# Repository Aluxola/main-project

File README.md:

# main-project
# Micro-mouse System Power and Sensor Subsystems
# Overview
This repository contains the design and implementation files for the Power and Sensor subsystems of a robotic system developed as part of the EEE3088F_2024 project. The Power subsystem manages power distribution, voltage regulation, and battery management, while the Sensor subsystem handles sensing and feedback for the robot's environment.

# Power Subsystem Features
Power distribution to motors and electronic components
Voltage regulation for stable operation
Battery management functions for efficient use
Current limiting and safety features
Power switching capabilities for control
Efficiency optimization for energy savings
# Sensor Subsystem Features
Wall sensing using infrared sensors
LED indicators for wall detection
Interface with the processor board for feedback
Low power consumption design
Reliability and accuracy in sensing wall proximity
# Contents
## Power Module:
### Schematics: 
Contains the schematic diagrams of the power module circuitry.
### PCB Design: 
Includes the PCB layout design files for manufacturing the power module.

## Sensor Module:
### Schematics: 
Contains the schematic diagrams of the sensor module circuitry.
### PCB Design: 
Includes the PCB layout design files for manufacturing the sensor module.
### Code: 
Firmware or software code for interfacing the sensor module with the processor board.
## Requirements
### Hardware: 
List of components required for building the power and sensor modules.
### Software: 
Tools and software required for programming, testing, and interfacing with the modules.

# Contributors
Alulutho Mthitshana

Tlangelani Tembe

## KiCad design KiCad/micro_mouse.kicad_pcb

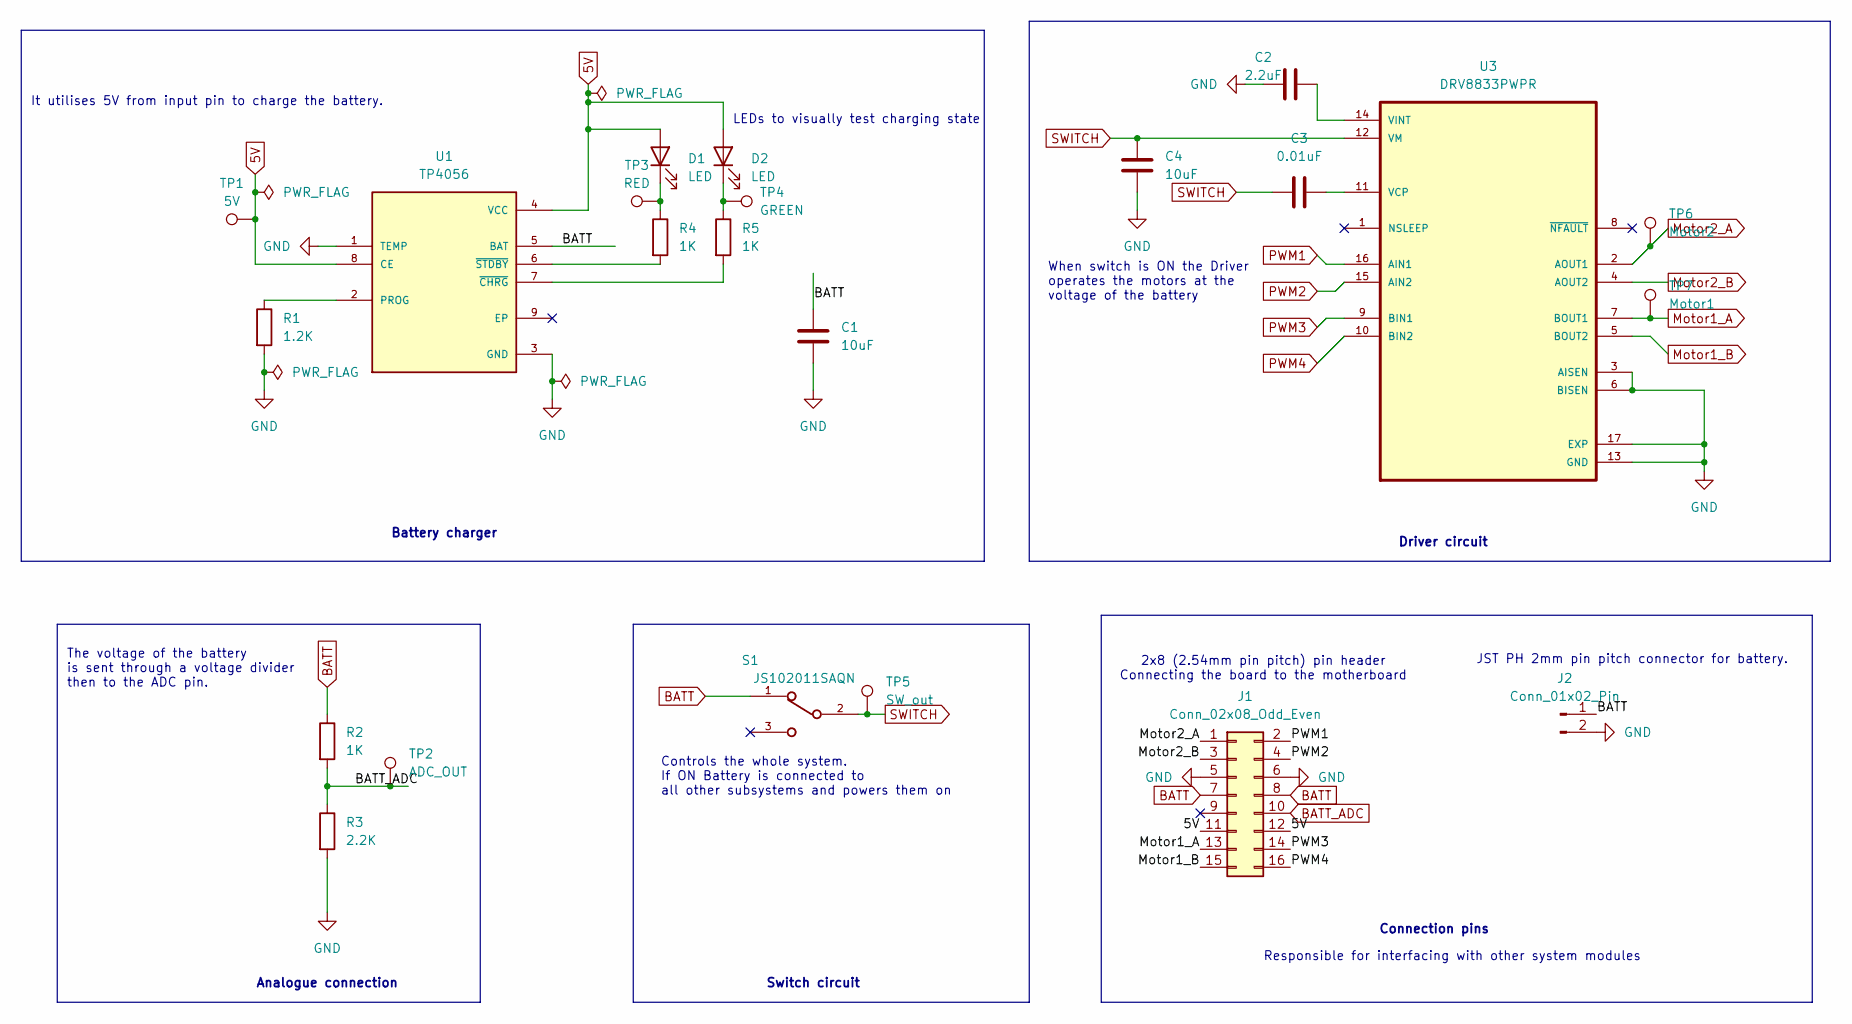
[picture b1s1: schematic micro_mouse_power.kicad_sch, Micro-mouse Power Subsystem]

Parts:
C1, C4: 10uF; C_0603_1608Metric
C2: 2.2uF; C_0603_1608Metric
C3: 0.01uF; C_0603_1608Metric
D1: LED; LED_0805_2012Metric
D2: LED; LED_0603_1608Metric
J1: Conn_02x08_Odd_Even; PinHeader_2x08_P2.54mm_Vertical
J2: Conn_01x02_Pin; JST_PH_B2B-PH-K_1x02_P2.00mm_Vertical
R1: 1.2K; R_0603_1608Metric
R2, R4, R5: 1K; R_0603_1608Metric
R3: 2.2K; R_0603_1608Metric
S1: JS102011SAQN; SW_JS102011SAQN
TP1: 5V; TestPoint_Pad_D1.5mm
TP2: ADC_OUT; TestPoint_Pad_D1.5mm
TP3: RED; TestPoint_Pad_D1.5mm
TP4: GREEN; TestPoint_Pad_D1.5mm
TP5: SW_out
TP6: Motor2; TestPoint_Pad_D1.5mm
TP7: Motor1; TestPoint_Pad_D1.5mm
U1: TP4056; SOP127P600X175-9N
U3: DRV8833PWPR; SOP65P640X120-16N; PARTREV E

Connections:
5V: D1.2 (A), D2.2 (A), J1.11, J1.12, TP1.1, U1.4 (VCC), U1.8 (CE)
BATT: C1.2, J1.7, J1.8, J2.1, R2.1, S1.1, U1.5 (BAT)
BATT_ADC: J1.10, R2.2, R3.1, TP2.1
GND: C1.1, C2.1, C4.2, J1.5, J1.6, J2.2, R1.2, R3.2, U1.1 (TEMP), U1.3 (GND), U3.3 (AISEN), U3.6 (BISEN), U3.13 (GND), U3.17 (EXP); also elsewhere on the board
Motor1_A: J1.13, TP7.1, U3.7 (BOUT1); also elsewhere on the board
Motor1_B: J1.15; also elsewhere on the board
Motor2_A: J1.1, TP6.1, U3.2 (AOUT1); also elsewhere on the board
Motor2_B: J1.3; also elsewhere on the board
unnamed: D1.1 (K), R4.1, TP3.1
unnamed: D2.1 (K), R5.1, TP4.1
unnamed: R1.1, U1.2 (PROG)
unnamed: R5.2, U1.7 (~CHRG)
unnamed: R4.2, U1.6 (~STDBY)
unnamed: C3.2, U3.11 (VCP)
unnamed: C2.2, U3.14 (VINT)
PWM1: J1.2; also elsewhere on the board
PWM2: J1.4; also elsewhere on the board
PWM3: J1.14; also elsewhere on the board
PWM4: J1.16; also elsewhere on the board
SWITCH: C3.1, C4.1, S1.2, TP5.1, U3.12 (VM); also elsewhere on the board

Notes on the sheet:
Battery charger
2x8 (2.54mm pin pitch) pin header Connecting the board to the motherboard
Switch circuit
The voltage of the battery is sent through a voltage divider then to the ADC pin.
Controls the whole system. If ON Battery is connected to all other subsystems and powers them on
It utilises 5V from input pin to charge the battery.
LEDs to visually test charging state
Analogue connection
JST PH 2mm pin pitch connector for battery.
Driver circuit
Responsible for interfacing with other system modules
Connection pins
When switch is ON the Driver operates the motors at the voltage of the battery

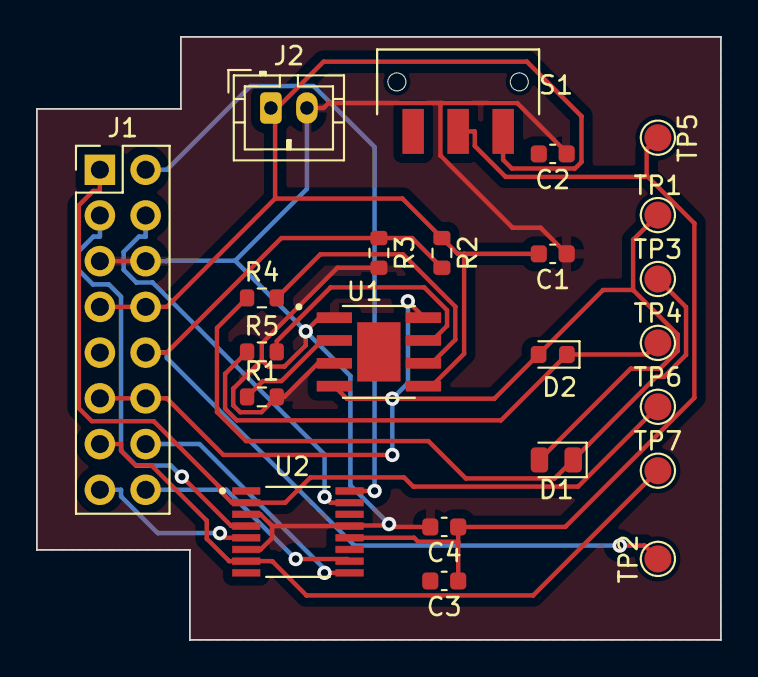
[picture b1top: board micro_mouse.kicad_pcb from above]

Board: 2 copper layers, 38.0 x 33.5 mm, 23 parts (0 on the bottom side), 18 nets.

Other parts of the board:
U2: DRV8833PW; SOP65P640X120-16N

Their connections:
GND: U2.3 (A_ISENSE), U2.6 (B_ISENSE), U2.13 (GND); also elsewhere on the board
Motor1_A: U2.7 (B_OUT1); also elsewhere on the board
Motor1_B: U2.5 (B_OUT2); also elsewhere on the board
Motor2_A: U2.2 (A_OUT1); also elsewhere on the board
Motor2_B: U2.4 (A_OUT2); also elsewhere on the board
PWM1: U2.16 (A_IN1); also elsewhere on the board
PWM2: U2.15 (A_IN2); also elsewhere on the board
PWM3: U2.9 (B_IN1); also elsewhere on the board
PWM4: U2.10 (B_IN2); also elsewhere on the board
SWITCH: U2.12 (VM); also elsewhere on the board

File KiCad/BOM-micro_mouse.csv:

Comment,Designator,Footprint,LCSC
10uF,"C1,C4",C_0603_1608Metric,C19702
1K,"R2,R4,R5",R_0603_1608Metric,C21190
JS102011SAQN,S1,SW_JS102011SAQN,C221660
1.2K,R1,R_0603_1608Metric,C22765
LED,D2,LED_0603_1608Metric,C2286
LED,D1,LED_0805_2012Metric,C2297
2.2uF,C2,C_0603_1608Metric,C23630
2.2K,R3,R_0603_1608Metric,C4190
DRV8833PW,U2,SOP65P640X120-16N,C50506
0.01uF,C3,C_0603_1608Metric,C57112
TP4056,U1,SOP127P600X175-9N,C725790

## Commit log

2024-04-21 Create Datasheets
2024-04-21 Create Gerber Files
2024-04-21 Create PCB Production Files
